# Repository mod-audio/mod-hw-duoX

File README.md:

mod-hw-duoX
===========

This repository contains the schematics and PCB design files for the MOD Duo X. 

The MOD DuoX bottom-board is done in Kicad 5. 
The other board (controller board) is done in Altium.

Please, use KiCAD 5 to edit the project.

The `master` branch has the most recent version of the bottom-board project, made for the Duo X. 

The `rev_20161129-updated` branch has the legacy production version of the MOD Duo boards. 

## License

Copyright (c) 2014-2026 MOD Audio Limited.

The hardware design files (schematics, PCB layouts, fabrication files, BOMs) are licensed under
[CC BY-NC-SA 4.0](https://creativecommons.org/licenses/by-nc-sa/4.0/) (see [`LICENSE`](LICENSE)).
You may study, modify, repair and build them for yourself, and share your changes under the same licence.
You may not use them commercially, for example to make or sell boards or devices.

Third-party files (manufacturer component models, symbols and footprints, module documentation) are not covered by
this licence. See [`NOTICE`](NOTICE) for the list.

The MOD logo is a registered trademark (EU trade mark no. 016228827; UK trade mark no. UK00916228827).
The licence gives no right to use the MOD name or logo. See [`NOTICE`](NOTICE).

For commercial licensing, contact MOD Audio.

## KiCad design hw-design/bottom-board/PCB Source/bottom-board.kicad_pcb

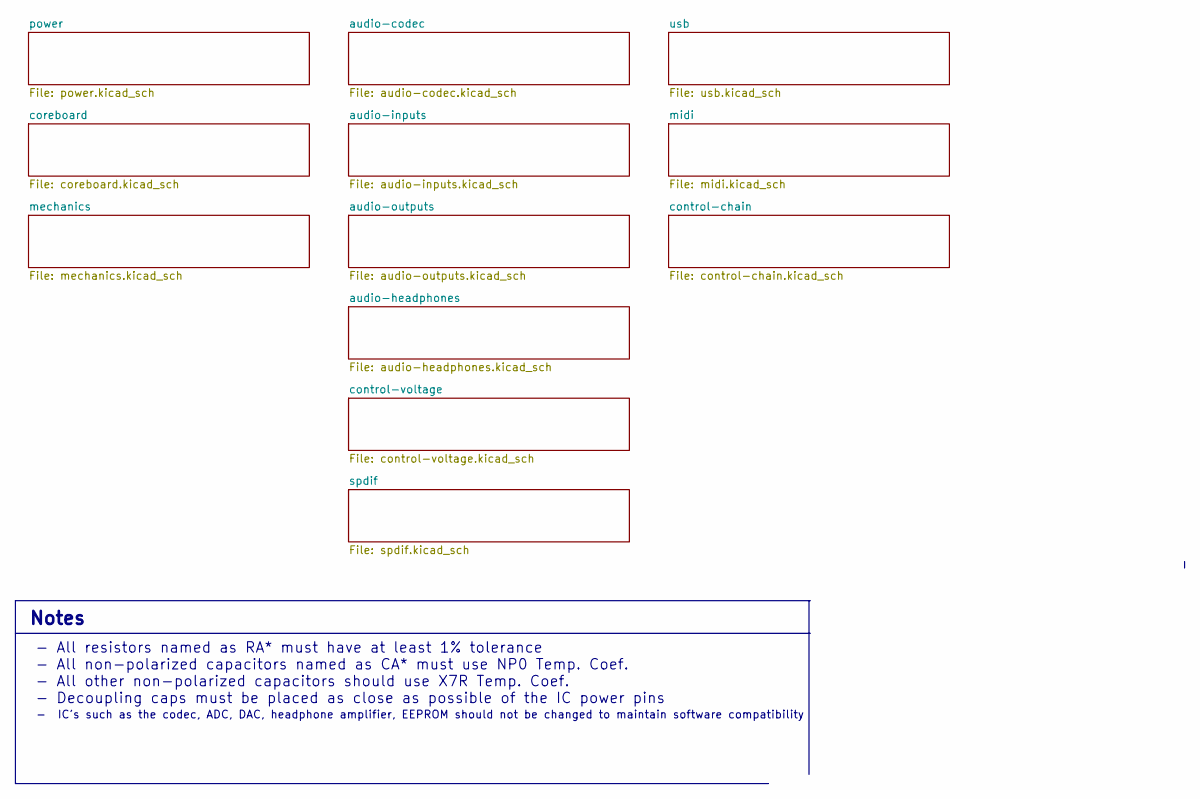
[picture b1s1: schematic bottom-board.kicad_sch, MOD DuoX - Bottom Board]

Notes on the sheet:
- IC's such as the codec, ADC, DAC, headphone amplifier, EEPROM should not be changed to maintain software compatibility
- All resistors named as RA* must have at least 1% tolerance - All non-polarized capacitors named as CA* must use NP0 Temp. Coef. - All other non-polarized capacitors should use X7R Temp. Coef. - Decoupling caps must be placed as close as possible of the IC power pins
Notes

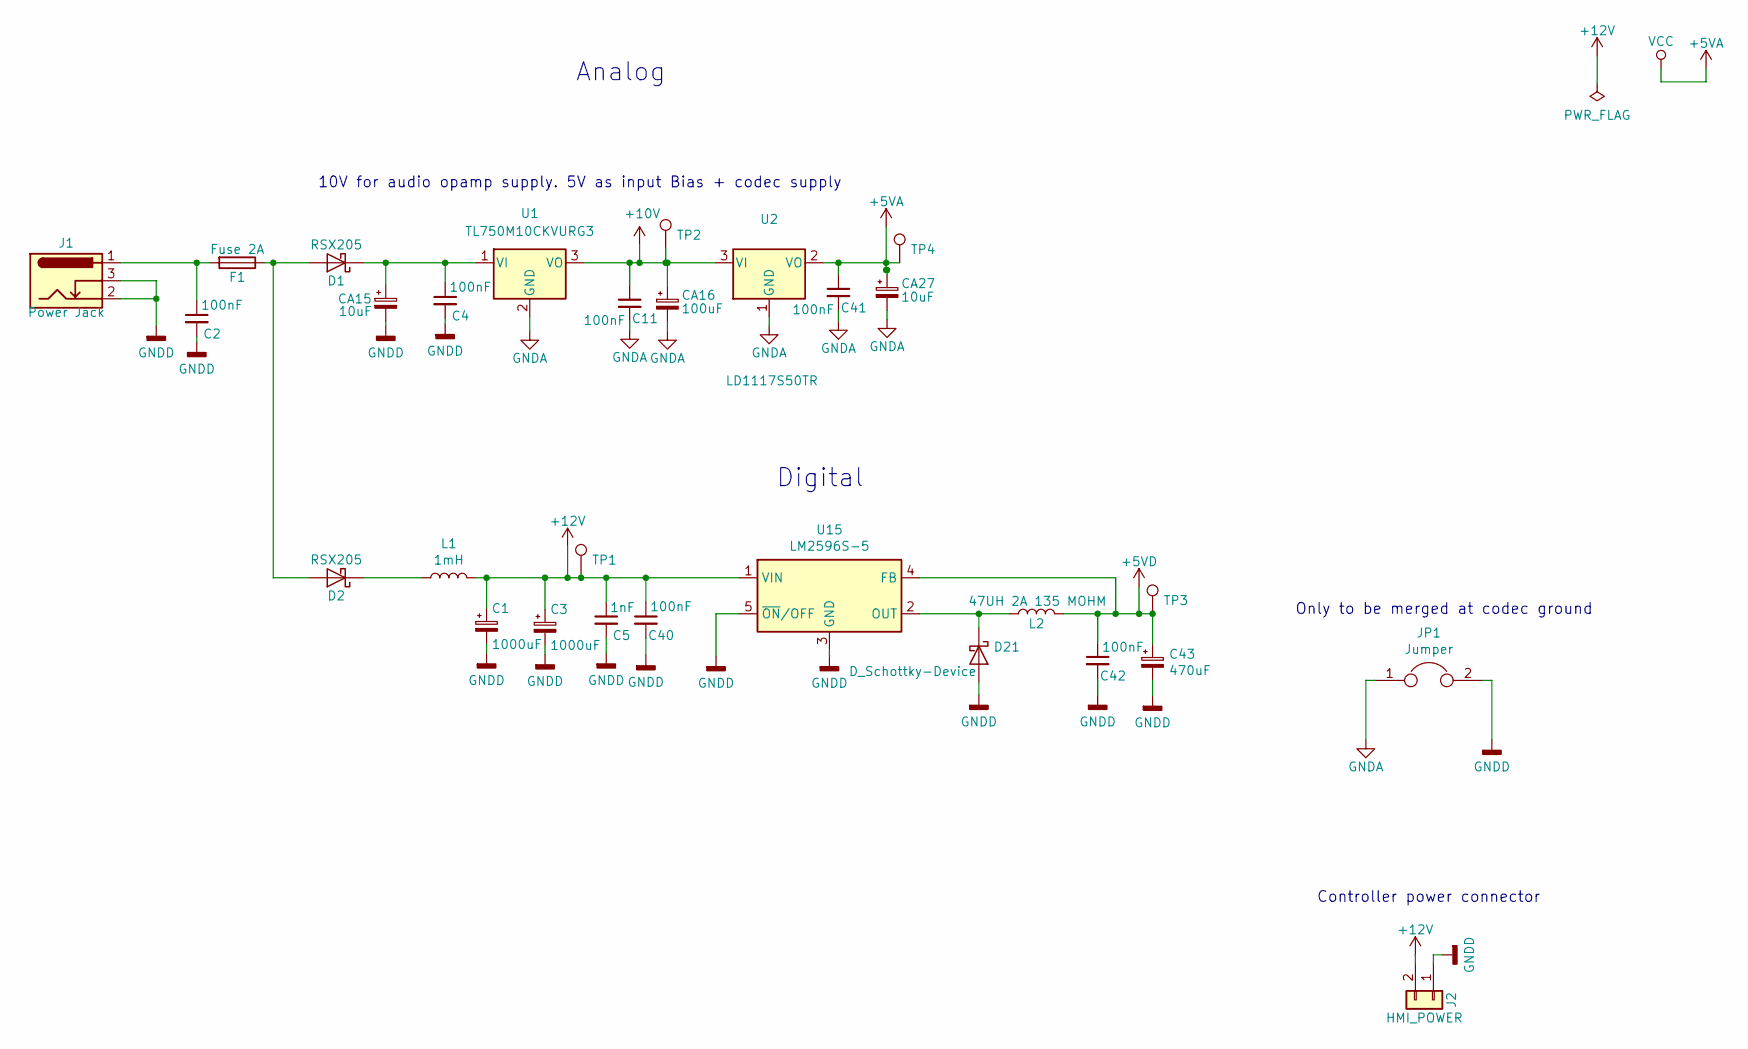
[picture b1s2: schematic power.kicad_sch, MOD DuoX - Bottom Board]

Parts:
C1, C3: 1000uF; CP_Elec_10x10.5; MPN UCM1C102MNL1GS
C2, C4, C11, C40, C41, C42: 100nF; C_0603_1608Metric; MPN GCM188R71C104KA37D
C5: 1nF; C_0603_1608Metric; MPN C0603X7R500-103KNP
C43: 470uF; CP_Elec_8x10.5; MPN UCW1C471MNL1GS
CA15, CA27: 10uF; CP_Elec_4x5.7; MPN EEE-HB1C100R
CA16: 100uF; CP_Elec_6.3x7.7; MPN 107SML016M
D1, D2: RSX205; D_SOD-123F; MPN RSX205LAM30TR
D21: D_Schottky-Device; D_MELF; MPN TSSA3U45 R3G
F1: Fuse 2A; Fuse_2920_0ZCF_Bel; MPN 0ZCF0200FF2C
J1: Power Jack; BarrelJack_Horizontal; MPN Adafruit Industries LLC 3643
J2: HMI_POWER; B2B-XH-A; MPN B2B-XH-A(LF)(SN)
JP1: Jumper; SolderJumper-2_P1.3mm_Bridged2Bar_RoundedPad1.0x1.5mm
L1: 1mH; L_Bourns_SRR1260; MPN SRR1260-102K
L2: 47UH 2A 135 MOHM; SRN8040TA; MPN SRN8040TA-470M
TP1, TP2, TP3, TP4: TestPoint; TestPoint_Pad_D1.0mm
U1: TL750M10CKVURG3; TO-252-3_TabPin2; MPN TL750M10CKVURG3
U2: LD1117S50TR; SOT-223-3_TabPin2; MPN LD1117S50TR
U15: LM2596S-5; TO-263-5_TabPin3; MPN TS2596CM550 RNG

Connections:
+5VA: C41.1, CA27.1, TP4.1, U2.2 (VO); also elsewhere on the board
+5VD: C42.1, C43.1, L2.2, TP3.1, U15.4 (FB); also elsewhere on the board
+12V: C1.1, C3.1, C5.1, C40.1, J2.2, L1.2, TP1.1, U15.1 (VIN); also elsewhere on the board
GNDD: C1.2, C2.2, C3.2, C4.2, C5.2, C40.2, C42.2, C43.2, CA15.2, D21.2 (A), J1.2, J1.3, J2.1, JP1.2, U15.3 (GND), U15.5 (~ON/OFF); also elsewhere on the board
unnamed: C2.1, F1.2, J1.1
unnamed: D1.2 (A), D2.2 (A), F1.1
unnamed: D2.1 (K), L1.1
unnamed: D21.1 (K), L2.1, U15.2 (OUT)

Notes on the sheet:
10V for audio opamp supply. 5V as input Bias + codec supply
Only to be merged at codec ground
Digital
Controller power connector
Analog

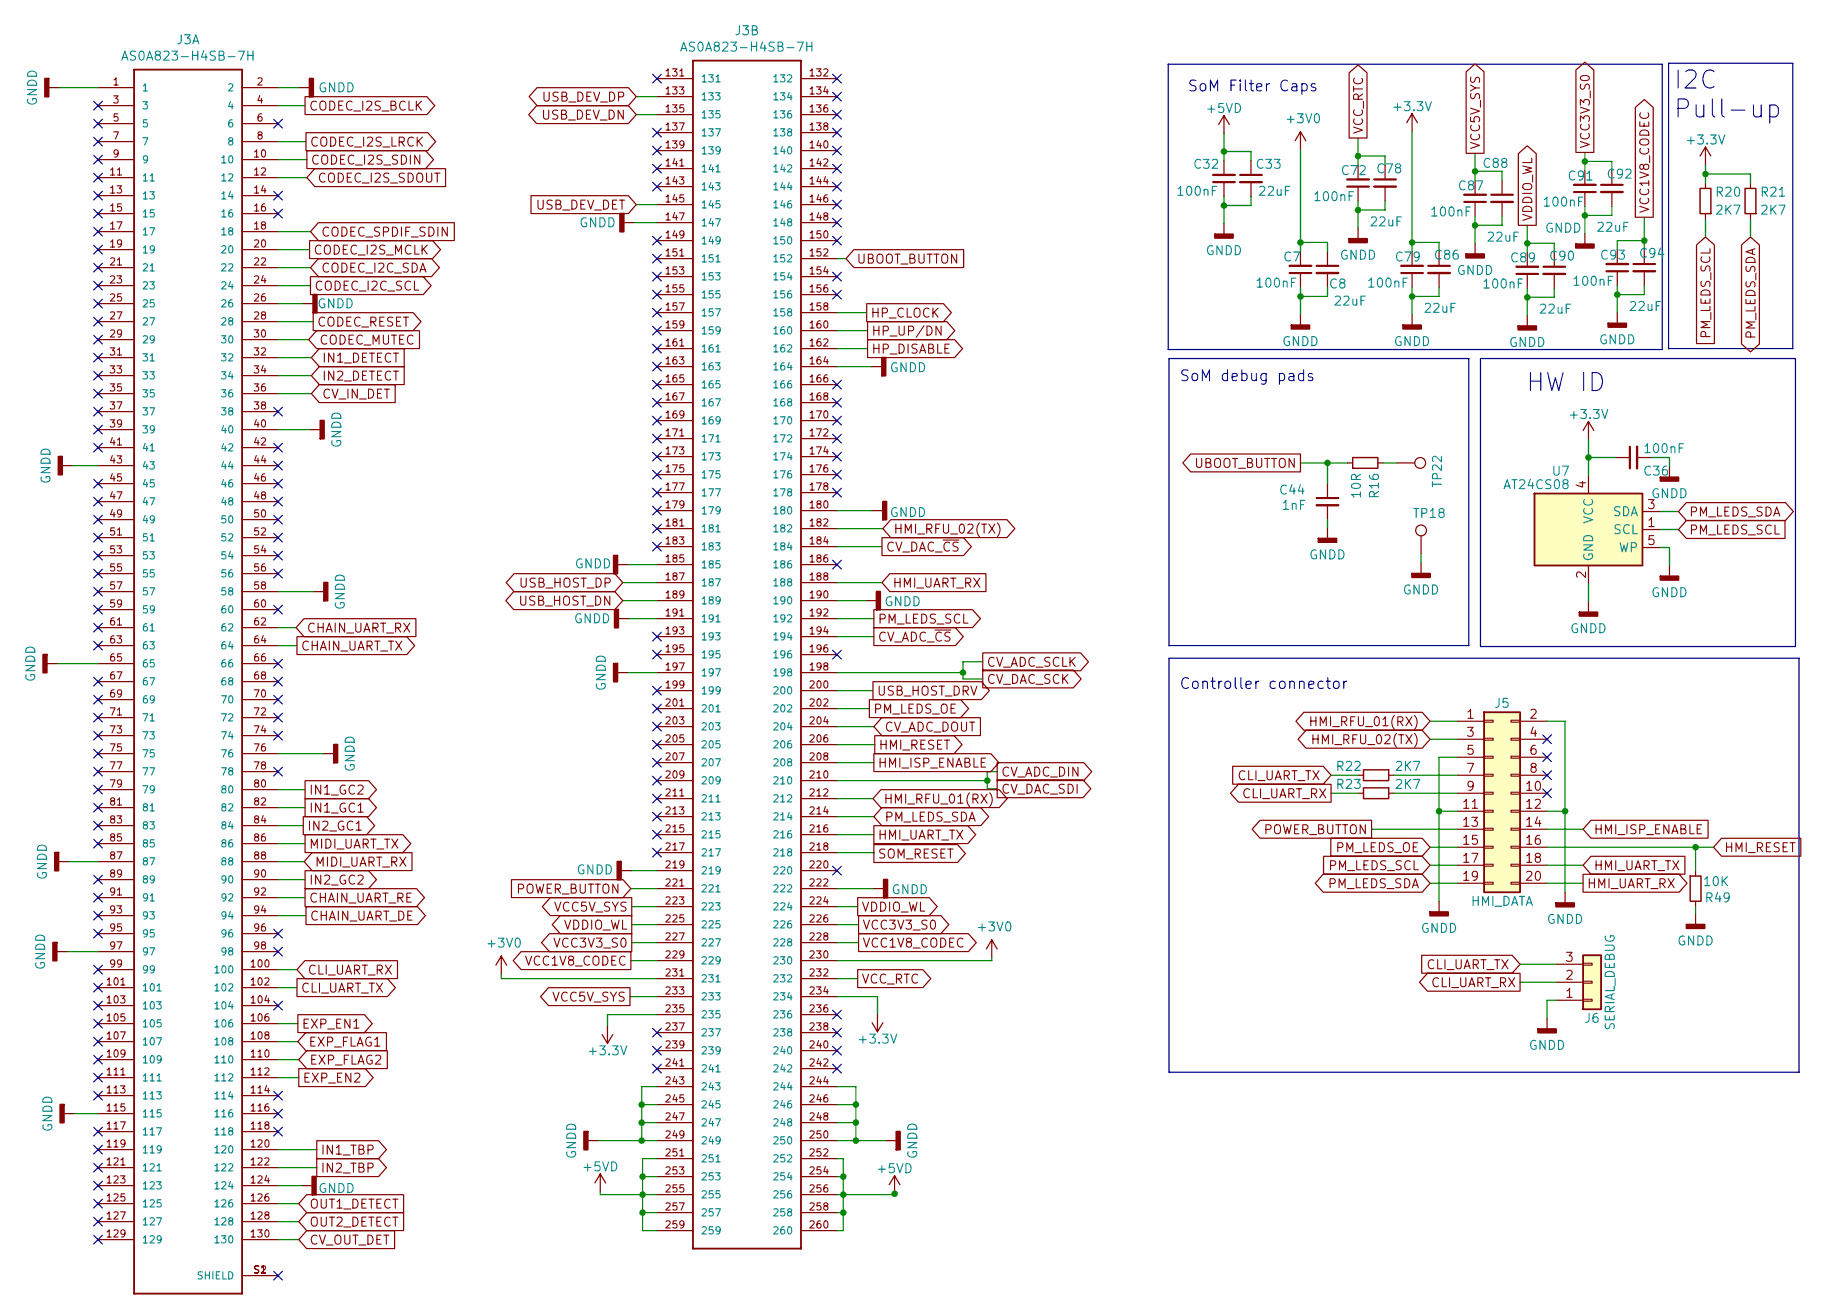
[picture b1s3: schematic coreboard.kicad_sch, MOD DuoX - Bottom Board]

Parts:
C7, C32, C36, C72, C79, C87, C89, C91, C93: 100nF; C_0603_1608Metric; MPN GCM188R71C104KA37D
C8, C33, C78, C86, C88, C90, C92, C94: 22uF; C_0805_2012Metric; MPN CL21A226MPQNNNE
C44: 1nF; C_0603_1608Metric; MPN C0603X7R500-103KNP
J3: AS0A823-H4SB-7H; TE_2309409-1; MPN TE_2309409-1
J5: HMI_DATA; Pin_Header_Straight_2x10_Shrouded; MPN SBH11-PBPC-D10-ST-BK
J6: SERIAL_DEBUG; PinHeader_1x03_P2.54mm_Vertical; MPN DO NOT PLACE
R16: 10R; R_0603_1608Metric; MPN CRGCQ0603J10R
R20, R21, R22, R23: 2K7; R_0603_1608Metric; MPN CRGCQ0603F2K7
R49: 10K; R_0603_1608Metric; MPN RR0816P-103-D
TP18, TP22: TestPoint; TestPoint_Loop_D1.80mm_Drill1.0mm_Beaded
U7: AT24CS08; SOT-23-5; MPN AT24CS08-STUM-T

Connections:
+3V0: C7.2, C8.1, J3.230, J3.231
+3V3: C36.1, C79.2, C86.1, J3.234, J3.235, R20.2, R21.2, U7.4 (VCC)
+5VD: C32.2, C33.1, J3.251, J3.252, J3.253, J3.254, J3.255, J3.256, J3.257, J3.258, J3.259, J3.260; also elsewhere on the board
CHAIN_UART_DE: J3.94; also elsewhere on the board
CHAIN_UART_RE: J3.92; also elsewhere on the board
CHAIN_UART_RX: J3.62; also elsewhere on the board
CHAIN_UART_TX: J3.64; also elsewhere on the board
CLI_UART_RX: J3.100, J6.2, R23.2
CLI_UART_TX: J3.102, J6.3, R22.2
CODEC_I2C_SCL: J3.24; also elsewhere on the board
CODEC_I2C_SDA: J3.22; also elsewhere on the board
CODEC_I2S_BCLK: J3.4; also elsewhere on the board
CODEC_I2S_LRCK: J3.8; also elsewhere on the board
CODEC_I2S_MCLK: J3.20; also elsewhere on the board
CODEC_I2S_SDIN: J3.10; also elsewhere on the board
CODEC_I2S_SDOUT: J3.12; also elsewhere on the board
CODEC_MUTEC: J3.30; also elsewhere on the board
CODEC_RESET: J3.28; also elsewhere on the board
CODEC_SPDIF_SDIN: J3.18; also elsewhere on the board
CV_ADC_DIN: J3.210; also elsewhere on the board
CV_ADC_DOUT: J3.204; also elsewhere on the board
CV_ADC_SCLK: J3.198; also elsewhere on the board
CV_ADC_~CS~: J3.194; also elsewhere on the board
CV_DAC_~CS~: J3.184; also elsewhere on the board
CV_IN_DET: J3.36; also elsewhere on the board
CV_OUT_DET: J3.130; also elsewhere on the board
EXP_EN1: J3.106; also elsewhere on the board
EXP_EN2: J3.112; also elsewhere on the board
EXP_FLAG1: J3.108; also elsewhere on the board
EXP_FLAG2: J3.110; also elsewhere on the board
GNDD: C7.1, C8.2, C32.1, C33.2, C36.2, C44.2, C72.1, C78.2, C79.1, C86.2, C87.1, C88.2, C89.1, C90.2, C91.1, C92.2, C93.1, C94.2, J3.1, J3.2, J3.26, J3.40, J3.43, J3.58, J3.65, J3.76, J3.87, J3.97, J3.115, J3.124, J3.147, J3.164, J3.180, J3.185, J3.190, J3.191, J3.197, J3.219, J3.222, J3.243, J3.244, J3.245, J3.246, J3.247, J3.248, J3.249, J3.250, J5.2, J5.5, J5.11, J5.12, J6.1, R49.2, TP18.1, U7.2 (GND), U7.5 (WP); also elsewhere on the board
HMI_ISP_ENABLE: J3.208, J5.14
HMI_RESET: J3.206, J5.16, R49.1
HMI_RFU_01(RX): J3.212, J5.1
HMI_RFU_02(TX): J3.182, J5.3
HMI_UART_RX: J3.188, J5.20
HMI_UART_TX: J3.216, J5.18
HP_CLOCK: J3.158; also elsewhere on the board
HP_DISABLE: J3.162; also elsewhere on the board
HP_UP/DN: J3.160; also elsewhere on the board
IN1_DETECT: J3.32; also elsewhere on the board
IN1_GC1: J3.82; also elsewhere on the board
IN1_GC2: J3.80; also elsewhere on the board
IN1_TBP: J3.120; also elsewhere on the board
IN2_DETECT: J3.34; also elsewhere on the board
IN2_GC1: J3.84; also elsewhere on the board
IN2_GC2: J3.90; also elsewhere on the board
IN2_TBP: J3.122; also elsewhere on the board
MIDI_UART_RX: J3.88; also elsewhere on the board
MIDI_UART_TX: J3.86; also elsewhere on the board
unnamed: J3.S1 (SHIELD), J3.S2 (SHIELD)
unnamed: J5.7, R22.1
unnamed: J5.9, R23.1
unnamed: R16.2, TP22.1
OUT1_DETECT: J3.126; also elsewhere on the board
OUT2_DETECT: J3.128; also elsewhere on the board
PM_LEDS_OE: J3.202, J5.15
PM_LEDS_SCL: J3.192, J5.17, R20.1, U7.1 (SCL)
PM_LEDS_SDA: J3.214, J5.19, R21.1, U7.3 (SDA)
POWER_BUTTON: J3.221, J5.13
UBOOT_BUTTON: C44.1, J3.152, R16.1
USB_DEV_DET: J3.145; also elsewhere on the board
USB_DEV_DN: J3.135; also elsewhere on the board
USB_DEV_DP: J3.133; also elsewhere on the board
USB_HOST_DN: J3.189; also elsewhere on the board
USB_HOST_DP: J3.187; also elsewhere on the board
USB_HOST_DRV: J3.200; also elsewhere on the board
VCC1V8_CODEC: C93.2, C94.1, J3.228, J3.229
VCC3V3_S0: C91.2, C92.1, J3.226, J3.227
VCC5V_SYS: C87.2, C88.1, J3.223, J3.233
VCC_RTC: C72.2, C78.1, J3.232
VDDIO_WL: C89.2, C90.1, J3.224, J3.225

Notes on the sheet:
SoM debug pads
I2C Pull-up
SoM Filter Caps
Controller connector
HW ID

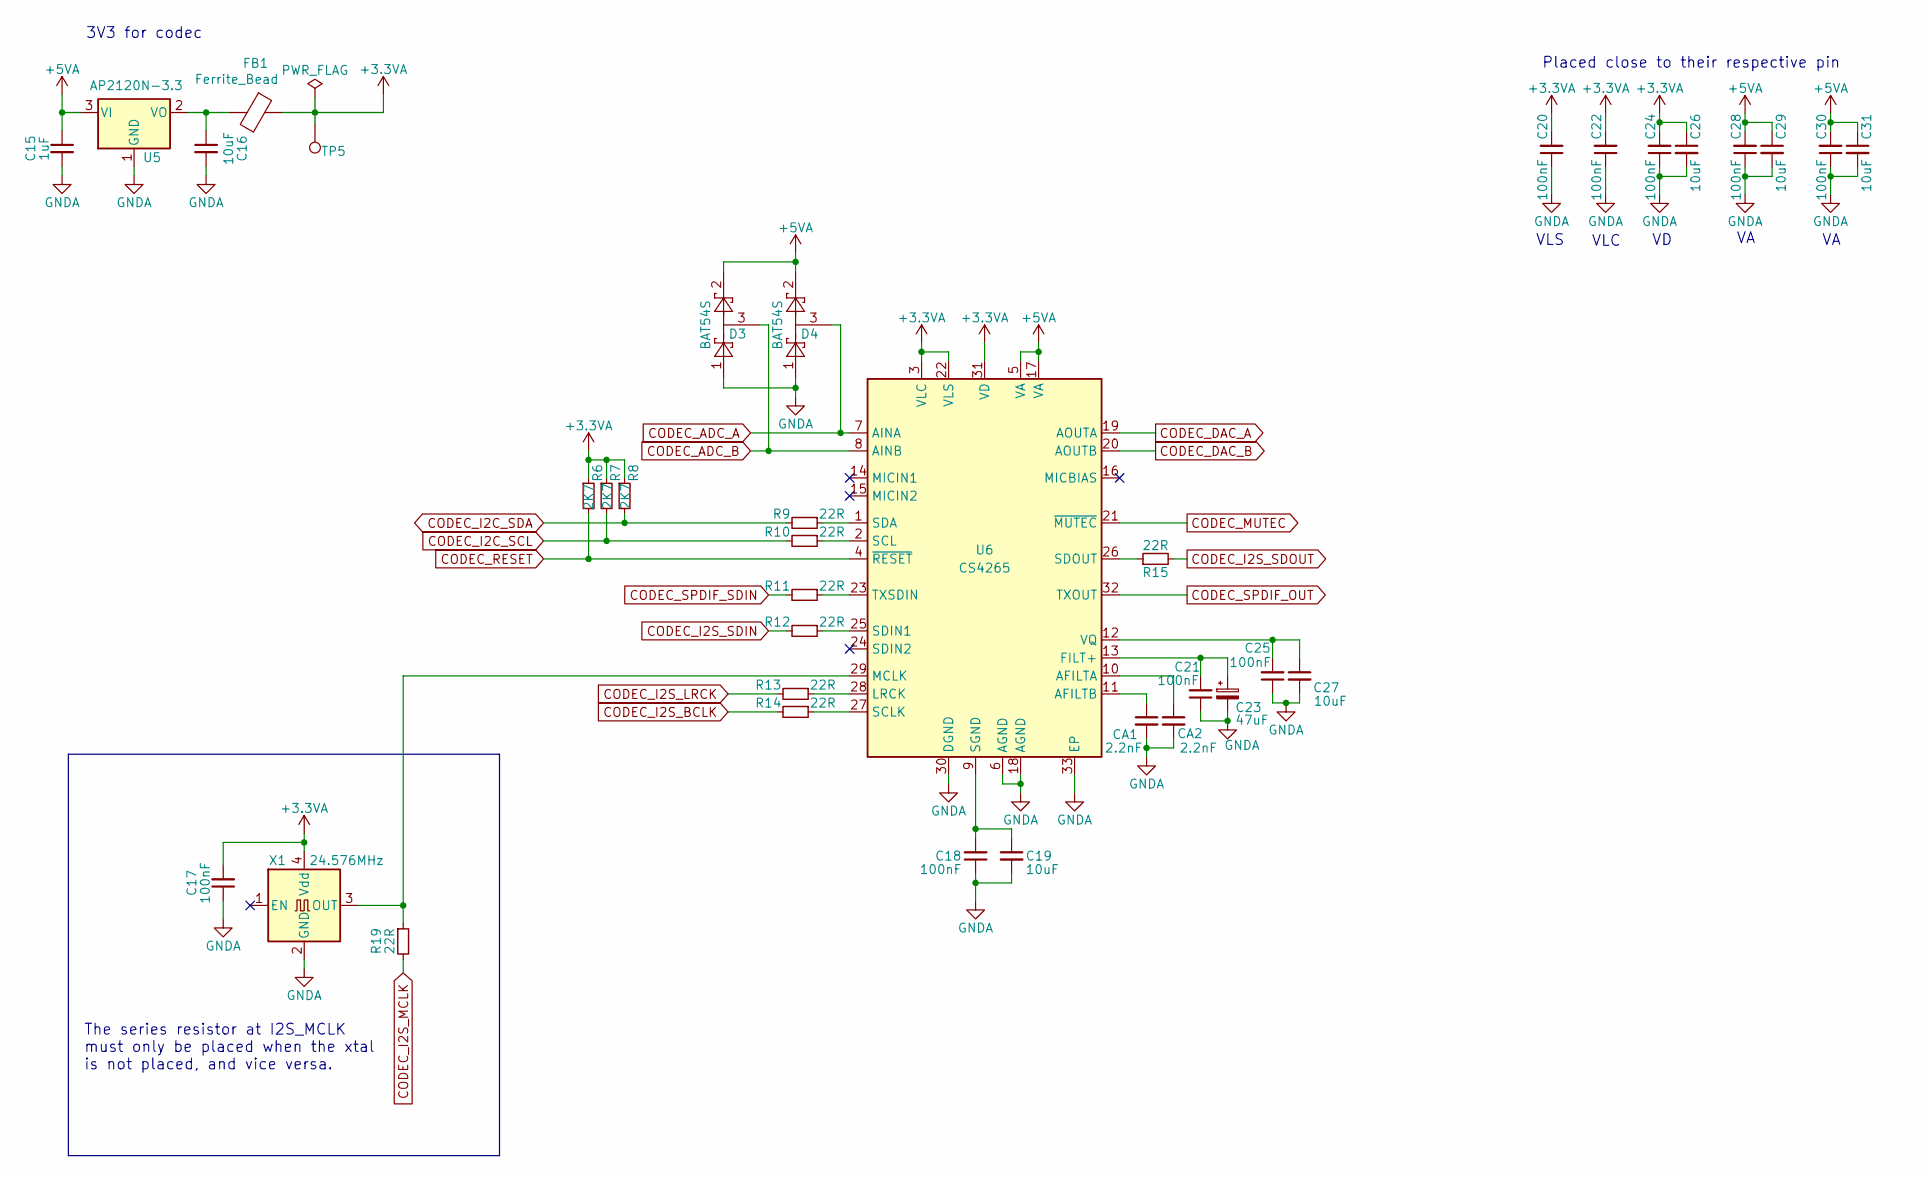
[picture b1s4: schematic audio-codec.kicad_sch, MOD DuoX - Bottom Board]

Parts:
C15: 1uF; C_0603_1608Metric; MPN TMK107B7105KA-T
C16, C19, C26, C27, C29, C31: 10uF; C_0805_2012Metric; MPN GRM219R61E106KA12D
C17, C18, C20, C21, C22, C24, C25, C28, C30: 100nF; C_0603_1608Metric; MPN GCM188R71C104KA37D
C23: 47uF; CP_Elec_5x5.4; MPN EDK476M016A9DAA
CA1, CA2: 2.2nF; C_0603_1608Metric; MPN GRM1885C1H222JA01D
D3, D4: BAT54S; SOT-23; MPN BAT54SFILM
FB1: Ferrite_Bead; R_0603_1608Metric; MPN BLM18HD102SH1D
R6, R7, R8: 2K7; R_0603_1608Metric; MPN CRGCQ0603F2K7
R9, R10, R11, R12, R13, R14, R15: 22R; R_0603_1608Metric; MPN RMCF0603JT22R0
R19: 22R; R_0603_1608Metric; MPN DO NOT PLACE
TP5: TestPoint; TestPoint_Pad_D1.0mm
U5: AP2120N-3.3; SOT-23; MPN AP2120N-3.3TRG1
U6: CS4265; QFN-32-1EP_5x5mm_P0.5mm_EP3.1x3.1mm; MPN CS4265-CNZ
X1: 24.576MHz; Oscillator_SMD_Abracon_ASV-4Pin_7.0x5.1mm; MPN ASV-24.576MHZ-EJ-T

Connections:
+3.3VA: C17.2, C20.2, C22.2, C24.2, C26.1, FB1.1, R6.1, R7.1, R8.1, TP5.1, U6.3 (VLC), U6.22 (VLS), U6.31 (VD), X1.4 (Vdd)
+5VA: C15.1, C28.2, C29.1, C30.2, C31.1, D3.2, D4.2, U5.3 (VI), U6.5 (VA), U6.17 (VA); also elsewhere on the board
CODEC_ADC_A: D4.3, U6.7 (AINA); also elsewhere on the board
CODEC_ADC_B: D3.3, U6.8 (AINB); also elsewhere on the board
CODEC_DAC_A: U6.19 (AOUTA); also elsewhere on the board
CODEC_DAC_B: U6.20 (AOUTB); also elsewhere on the board
CODEC_I2C_SCL: R7.2, R10.2; also elsewhere on the board
CODEC_I2C_SDA: R8.2, R9.2; also elsewhere on the board
CODEC_I2S_BCLK: R14.2; also elsewhere on the board
CODEC_I2S_LRCK: R13.2; also elsewhere on the board
CODEC_I2S_MCLK: R19.2; also elsewhere on the board
CODEC_I2S_SDIN: R12.2; also elsewhere on the board
CODEC_I2S_SDOUT: R15.2; also elsewhere on the board
CODEC_MUTEC: U6.21 (~MUTEC); also elsewhere on the board
CODEC_RESET: R6.2, U6.4 (~RESET); also elsewhere on the board
CODEC_SPDIF_OUT: U6.32 (TXOUT); also elsewhere on the board
CODEC_SPDIF_SDIN: R11.2; also elsewhere on the board
unnamed: C16.1, FB1.2, U5.2 (VO)
unnamed: C18.2, C19.1, U6.9 (SGND)
unnamed: C21.2, C23.1, U6.13 (FILT+)
unnamed: C25.2, C27.1, U6.12 (VQ)
unnamed: CA1.1, U6.11 (AFILTB)
unnamed: CA2.1, U6.10 (AFILTA)
unnamed: R9.1, U6.1 (SDA)
unnamed: R10.1, U6.2 (SCL)
unnamed: R11.1, U6.23 (TXSDIN)
unnamed: R12.1, U6.25 (SDIN1)
unnamed: R13.1, U6.28 (LRCK)
unnamed: R14.1, U6.27 (SCLK)
unnamed: R15.1, U6.26 (SDOUT)
unnamed: R19.1, U6.29 (MCLK), X1.3 (OUT)

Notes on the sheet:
3V3 for codec
Placed close to their respective pin
VLC
The series resistor at I2S_MCLK must only be placed when the xtal is not placed, and vice versa.
VLS

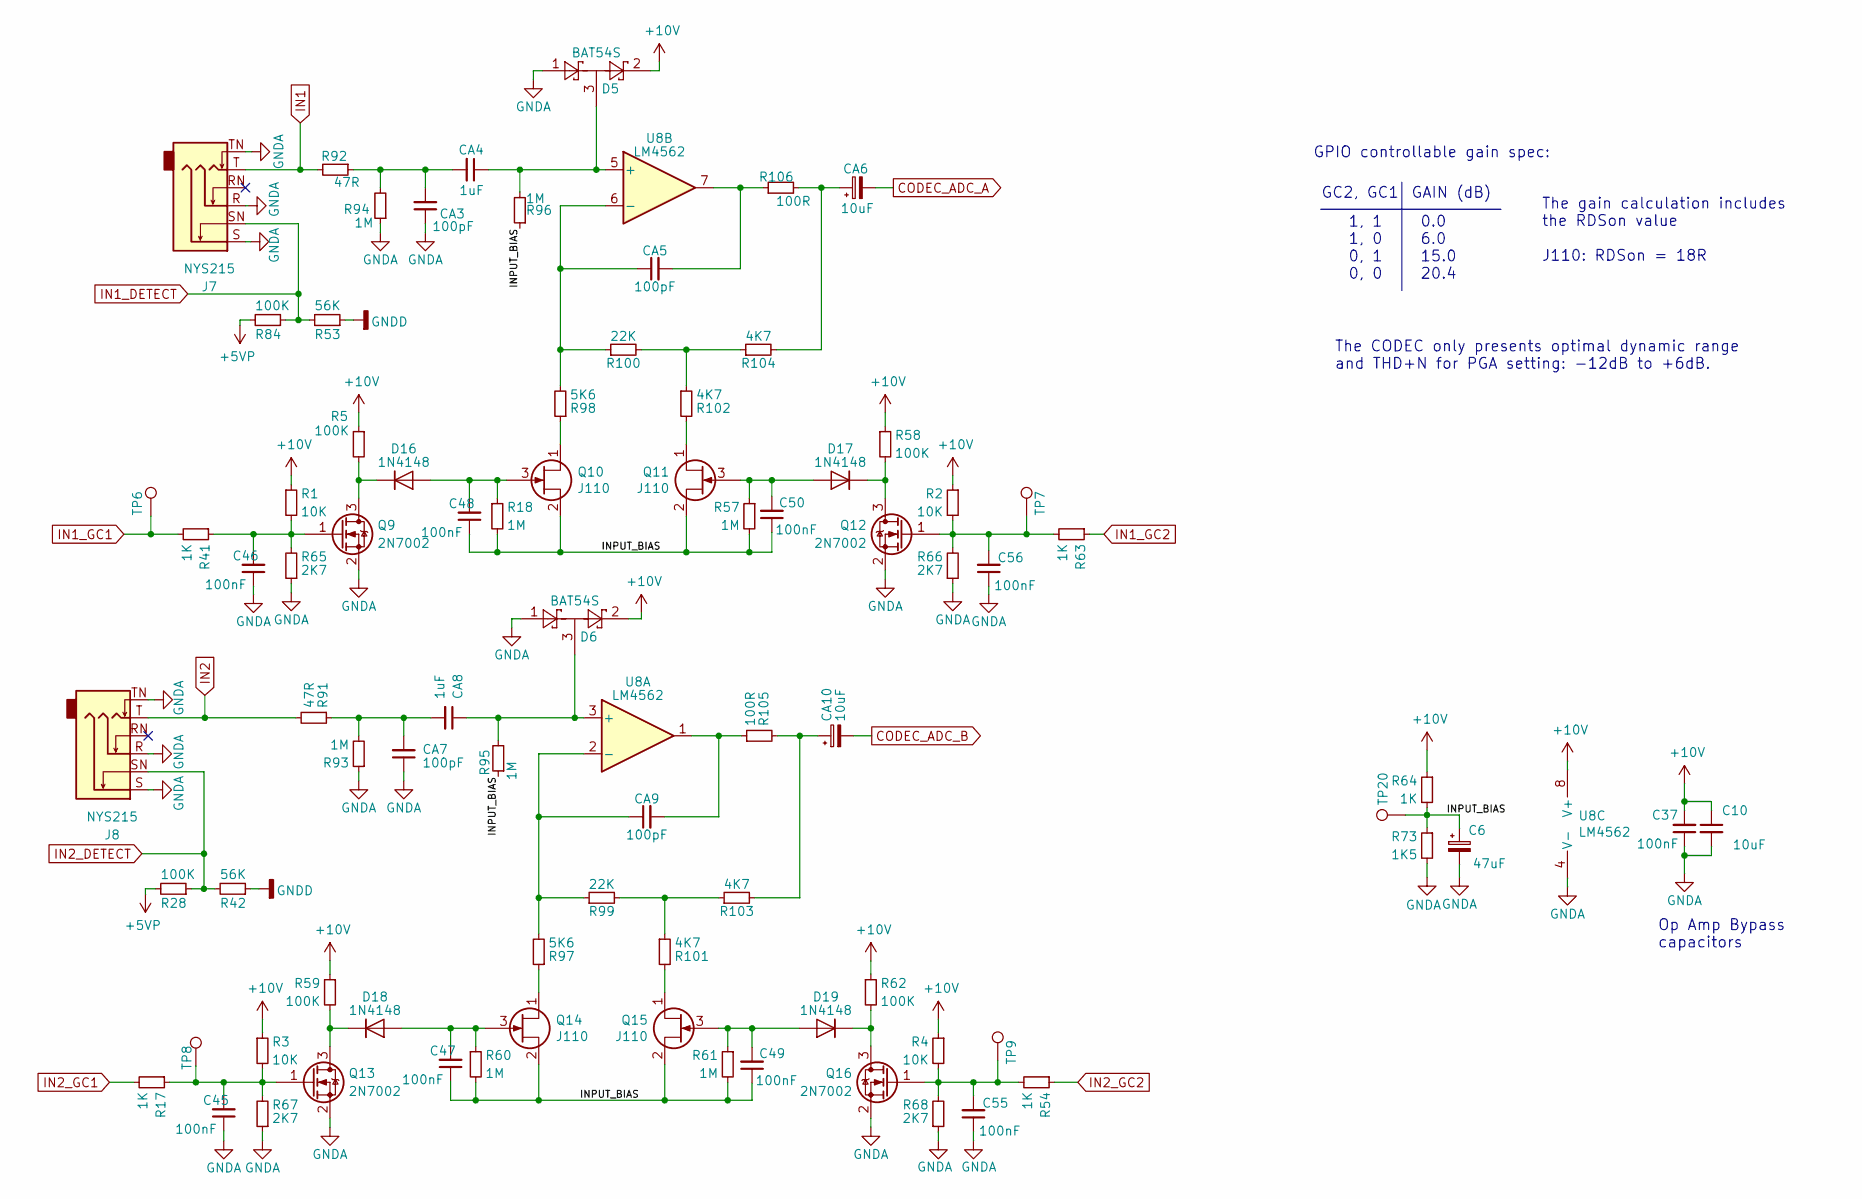
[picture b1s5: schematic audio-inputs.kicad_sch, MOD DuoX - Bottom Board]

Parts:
C6: 47uF; CP_Elec_5x5.4; MPN EDK476M016A9DAA
C10: 10uF; C_0805_2012Metric; MPN GRM219R61E106KA12D
C37, C45, C46, C47, C48, C49, C50, C55, C56: 100nF; C_0603_1608Metric; MPN GCM188R71C104KA37D
CA3, CA5, CA7, CA9: 100pF; C_0603_1608Metric; MPN C0603C101J3GACTU
CA4, CA8: 1uF; C_1210_3225Metric; MPN FCA1210C105M-G2
CA6, CA10: 10uF; CP_Elec_4x5.7; MPN EEE-HB1C100R
D5, D6: BAT54S; SOT-23; MPN BAT54SFILM
D16, D17, D18, D19: 1N4148; D_SOD-323; MPN 1N4148WX-TP
J7, J8: NYS215; NMJ6HCD2; MPN NYS215
Q9, Q12, Q13, Q16: 2N7002; SOT-23; MPN 2N7002P,215
Q10, Q11, Q14, Q15: J110; SOT-23; MPN MMBFJ110
R1, R2, R3, R4: 10K; R_0603_1608Metric; MPN RR0816P-103-D
R5, R28, R58, R59, R62, R84: 100K; R_0603_1608Metric; MPN RMCF0603JT100K
R17, R41, R54, R63, R64: 1K; R_0603_1608Metric; MPN ERJ-PB3D1001V
R18, R57, R60, R61, R93, R94, R95, R96: 1M; R_0603_1608Metric; MPN RT0603BRD071ML
R42, R53: 56K; R_0603_1608Metric; MPN RT0603DRD0756KL
R65, R66, R67, R68: 2K7; R_0603_1608Metric; MPN CRGCQ0603F2K7
R73: 1K5; R_0603_1608Metric; MPN CRGCQ0603F1K5
R91, R92: 47R; R_0603_1608Metric; MPN RT0603DRE0747RL
R97, R98: 5K6; R_0603_1608Metric; MPN ERA-3AED562V
R99, R100: 22K; R_0603_1608Metric; MPN RT0603DRD0722KL
R101, R102, R103, R104: 4K7; R_0603_1608Metric; MPN RT0603DRE074K7L
R105, R106: 100R; R_0603_1608Metric; MPN RT0603DRD07100RL
TP6, TP7, TP8, TP9, TP20: TestPoint; TestPoint_Pad_D1.0mm
U8: LM4562; SOIC-8_3.9x4.9mm_P1.27mm; MPN LM4562MAX/NOPB

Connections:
+5VP: R28.2, R84.2; also elsewhere on the board
/audio-inputs/INPUT_BIAS: C6.1, C47.1, C48.1, C49.1, C50.1, Q10.2 (S), Q11.2 (S), Q14.2 (S), Q15.2 (S), R18.2, R57.2, R60.2, R61.2, R64.2, R73.1, R95.1, R96.1, TP20.1
CODEC_ADC_A: CA6.2; also elsewhere on the board
CODEC_ADC_B: CA10.2; also elsewhere on the board
GNDD: R42.1, R53.1; also elsewhere on the board
IN1: J7.T, R92.2; also elsewhere on the board
IN1_DETECT: J7.SN, R53.2, R84.1; also elsewhere on the board
IN1_GC1: R41.2, TP6.1; also elsewhere on the board
IN1_GC2: R63.1; also elsewhere on the board
IN2: J8.T, R91.2; also elsewhere on the board
IN2_DETECT: J8.SN, R28.1, R42.2; also elsewhere on the board
IN2_GC1: R17.2; also elsewhere on the board
IN2_GC2: R54.1; also elsewhere on the board
unnamed: C45.2, Q13.1 (G), R3.2, R17.1, R67.2, TP8.1
unnamed: C46.2, Q9.1 (G), R1.2, R41.1, R65.2
unnamed: C47.2, D18.2 (A), Q14.3 (G), R60.1
unnamed: C48.2, D16.2 (A), Q10.3 (G), R18.1
unnamed: C49.2, D19.2 (A), Q15.3 (G), R61.1
unnamed: C50.2, D17.2 (A), Q11.3 (G), R57.1
unnamed: C55.2, Q16.1 (G), R4.2, R54.2, R68.2, TP9.1
unnamed: C56.2, Q12.1 (G), R2.2, R63.2, R66.2, TP7.1
unnamed: CA3.2, CA4.2, R92.1, R94.2
unnamed: CA4.1, D5.3, R96.2, U8.5 (+)
unnamed: CA5.1, R98.2, R100.1, U8.6 (-)
unnamed: CA5.2, R106.1, U8.7
unnamed: CA6.1, R104.2, R106.2
unnamed: CA7.2, CA8.2, R91.1, R93.2
unnamed: CA8.1, D6.3, R95.2, U8.3 (+)
unnamed: CA9.1, R97.2, R99.1, U8.2 (-)
unnamed: CA9.2, R105.1, U8.1
unnamed: CA10.1, R103.2, R105.2
unnamed: D16.1 (K), Q9.3 (D), R5.2
unnamed: D17.1 (K), Q12.3 (D), R58.2
unnamed: D18.1 (K), Q13.3 (D), R59.2
unnamed: D19.1 (K), Q16.3 (D), R62.2
unnamed: Q10.1 (D), R98.1
unnamed: Q11.1 (D), R102.2
unnamed: Q14.1 (D), R97.1
unnamed: Q15.1 (D), R101.2
unnamed: R100.2, R102.1, R104.1
unnamed: R99.2, R101.1, R103.1

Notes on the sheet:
GC2, GC1
GPIO controllable gain spec:
The CODEC only presents optimal dynamic range and THD+N for PGA setting: -12dB to +6dB.
The gain calculation includes the RDSon value J110: RDSon = 18R
Op Amp Bypass capacitors
GAIN (dB)
0.0 6.0 15.0 20.4
1, 1 1, 0 0, 1 0, 0

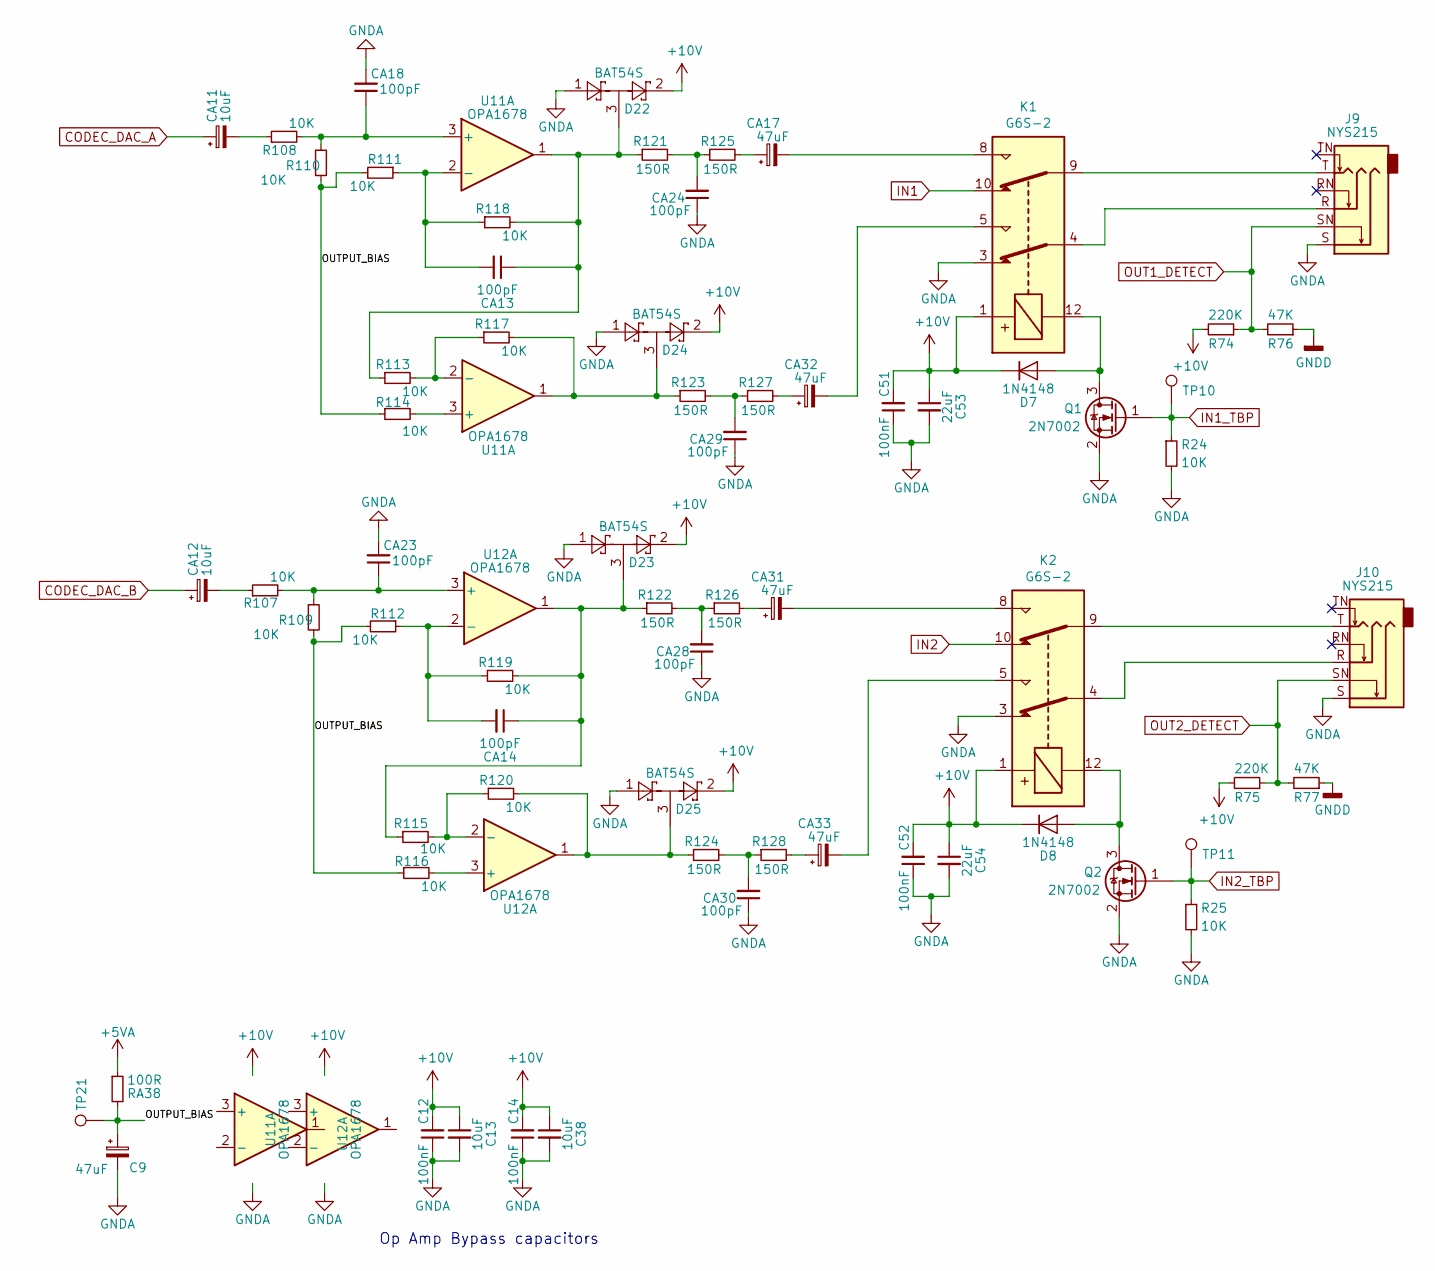
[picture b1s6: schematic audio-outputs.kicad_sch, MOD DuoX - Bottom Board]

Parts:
C9: 47uF; CP_Elec_5x5.4; MPN EDK476M016A9DAA
C12, C14, C51, C52: 100nF; C_0603_1608Metric; MPN GCM188R71C104KA37D
C13, C38: 10uF; C_0805_2012Metric; MPN GRM219R61E106KA12D
C53, C54: 22uF; C_0805_2012Metric; MPN CL21A226MPQNNNE
CA11, CA12: 10uF; CP_Elec_4x5.7; MPN EEE-HB1C100R
CA13, CA14, CA18, CA23, CA24, CA28, CA29, CA30: 100pF; C_0603_1608Metric; MPN C0603C101J3GACTU
CA17, CA31, CA32, CA33: 47uF; CP_Elec_6.3x7.7; MPN EDK476M016A9DAA
D7, D8: 1N4148; D_SOD-323; MPN 1N4148WX-TP
D22, D23, D24, D25: BAT54S; SOT-23; MPN BAT54SFILM
J9, J10: NYS215; NMJ6HCD2; MPN NYS215
K1, K2: G6S-2; Relay_DPDT_Omron_G6S-2F; MPN EE2-12NU-L
Q1, Q2: 2N7002; SOT-23; MPN 2N7002P,215
R24, R25, R107, R108, R109, R110, R111, R112, R113, R114, R115, R116, R117, R118, R119, R120: 10K; R_0603_1608Metric; MPN RR0816P-103-D
R74, R75: 220K; R_0603_1608Metric; MPN RMCF0603JT220K
R76, R77: 47K; R_0603_1608Metric; MPN RMCF0603JT47K0
R121, R122, R123, R124, R125, R126, R127, R128: 150R; R_0603_1608Metric; MPN RC0603FR-07150RL
RA38: 100R; R_0603_1608Metric; MPN RT0603DRD07100RL
TP10, TP11, TP21: TestPoint; TestPoint_Pad_D1.0mm
U11, U12: OPA1678; SOIC-8_3.9x4.9mm_P1.27mm; MPN OPA1678IDR

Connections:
+5VA: RA38.1; also elsewhere on the board
/audio-outputs/OUTPUT_BIAS: C9.1, R109.2, R110.2, R111.2, R112.2, R114.1, R116.1, RA38.2, TP21.1
CODEC_DAC_A: CA11.1; also elsewhere on the board
CODEC_DAC_B: CA12.1; also elsewhere on the board
GNDD: R76.1, R77.1; also elsewhere on the board
IN1: K1.10; also elsewhere on the board
IN1_TBP: Q1.1 (G), R24.1, TP10.1; also elsewhere on the board
IN2: K2.10; also elsewhere on the board
IN2_TBP: Q2.1 (G), R25.1, TP11.1; also elsewhere on the board
unnamed: CA11.2, R108.1
unnamed: CA12.2, R107.1
unnamed: CA17.1, R125.2
unnamed: CA17.2, K1.8
unnamed: CA24.2, R121.2, R125.1
unnamed: CA28.2, R122.2, R126.1
unnamed: CA29.2, R123.2, R127.1
unnamed: CA30.2, R124.2, R128.1
unnamed: CA31.1, R126.2
unnamed: CA31.2, K2.8
unnamed: CA32.1, R127.2
unnamed: CA32.2, K1.5
unnamed: CA33.1, R128.2
unnamed: CA33.2, K2.5
unnamed: D7.2 (A), K1.12, Q1.3 (D)
unnamed: D8.2 (A), K2.12, Q2.3 (D)
unnamed: J9.R, K1.4
unnamed: J9.T, K1.9
unnamed: J10.R, K2.4
unnamed: J10.T, K2.9
OUT1_DETECT: J9.SN, R74.1, R76.2; also elsewhere on the board
OUT2_DETECT: J10.SN, R75.1, R77.2; also elsewhere on the board

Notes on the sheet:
Op Amp Bypass capacitors

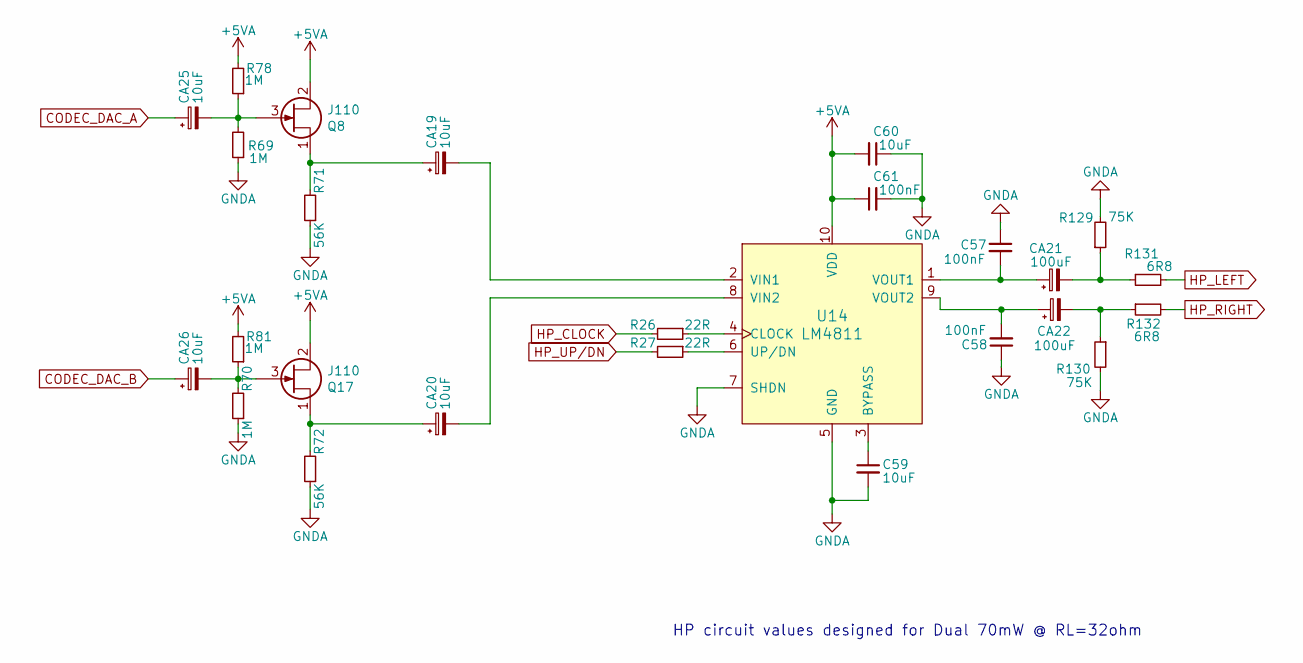
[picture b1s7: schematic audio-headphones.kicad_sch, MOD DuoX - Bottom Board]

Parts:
C57, C58, C61: 100nF; C_0603_1608Metric; MPN GCM188R71C104KA37D
C59, C60: 10uF; C_0805_2012Metric; MPN GRM219R61E106KA12D
CA19, CA20, CA25, CA26: 10uF; CP_Elec_4x5.7; MPN EEE-HB1C100R
CA21, CA22: 100uF; CP_Elec_6.3x7.7; MPN 107SML016M
Q8, Q17: J110; SOT-23; MPN MMBFJ110
R26, R27: 22R; R_0603_1608Metric; MPN RMCF0603JT22R0
R69, R70: 1M; R_0603_1608Metric; MPN RT0603BRD071ML
R71, R72: 56K; R_0603_1608Metric; MPN RT0603DRD0756KL
R78, R81: 1M; R_0603_1608Metric; MPN DO NOT PLACE
R129, R130: 75K; R_0603_1608Metric; MPN RR0816P-753-D
R131, R132: 6R8; R_0603_1608Metric; MPN RMCF0603FT6R80
U14: LM4811; MSOP-10_3x3mm_P0.5mm; MPN LM4811MM/NOPB

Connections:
+5VA: C60.2, C61.1, Q8.2 (S), Q17.2 (S), R78.2, R81.2, U14.10 (VDD); also elsewhere on the board
CODEC_DAC_A: CA25.1; also elsewhere on the board
CODEC_DAC_B: CA26.1; also elsewhere on the board
HP_CLOCK: R26.2; also elsewhere on the board
HP_LEFT: R131.2; also elsewhere on the board
HP_RIGHT: R132.2; also elsewhere on the board
HP_UP/DN: R27.2; also elsewhere on the board
unnamed: C57.2, CA21.1, U14.1 (VOUT1)
unnamed: C58.2, CA22.1, U14.9 (VOUT2)
unnamed: C59.1, U14.3 (BYPASS)
unnamed: CA19.1, Q8.1 (D), R71.2
unnamed: CA19.2, U14.2 (VIN1)
unnamed: CA20.1, Q17.1 (D), R72.2
unnamed: CA20.2, U14.8 (VIN2)
unnamed: CA21.2, R129.1, R131.1
unnamed: CA22.2, R130.1, R132.1
unnamed: CA25.2, Q8.3 (G), R69.2, R78.1
unnamed: CA26.2, Q17.3 (G), R70.2, R81.1
unnamed: R26.1, U14.4 (CLOCK)
unnamed: R27.1, U14.6 (UP/DN)

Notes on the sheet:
HP circuit values designed for Dual 70mW @ RL=32ohm
